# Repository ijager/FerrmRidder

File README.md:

# FerrmRidder

## Requirements

* Raspberry Pi 3 with Raspbian
* VL53L0X distance sensor
* Neopixel LED strip (WS2813)
* USB Audio output device (e.g. usb -> 3.5inch audio converter)
* Raspberry Pi breakout board with connectors for sensors (See Breakout directory)

## Installation Instructions

Download New Raspbian headless image and flash sd card

On a Mac:

```
diskutil unmountdisk /dev/disk2
sudo dd bs=2m if=2019-07-10-raspbian-buster-lite.img of=/dev/rdisk2
```

Boot raspberry pi and configure wifi and enable ssh and I2C

```
sudo raspi-config
```

Updates

```
sudo apt update && sudo apt upgrade
```

Install pip for python3
```
sudo apt-get install python3-pip
```

Install python dependencies, neopixel modules etc

```
sudo pip3 install rpi_ws281x adafruit-circuitpython-neopixel pygame libsdl-mixer1.2
sudo pip3 install adafruit-circuitpython-vl53l0x
sudo pip3 install adafruit-circuitpython-vl6180x
```

Then we'll follow [this Stackexchange](https://raspberrypi.stackexchange.com/questions/80072/how-can-i-use-an-external-usb-sound-card-and-set-it-as-default) answer to enable USB audio.

## send audio to pi

```
tar -czvf audio.tar.gz audio
scp audio.tar.gz pi@ip:~
```

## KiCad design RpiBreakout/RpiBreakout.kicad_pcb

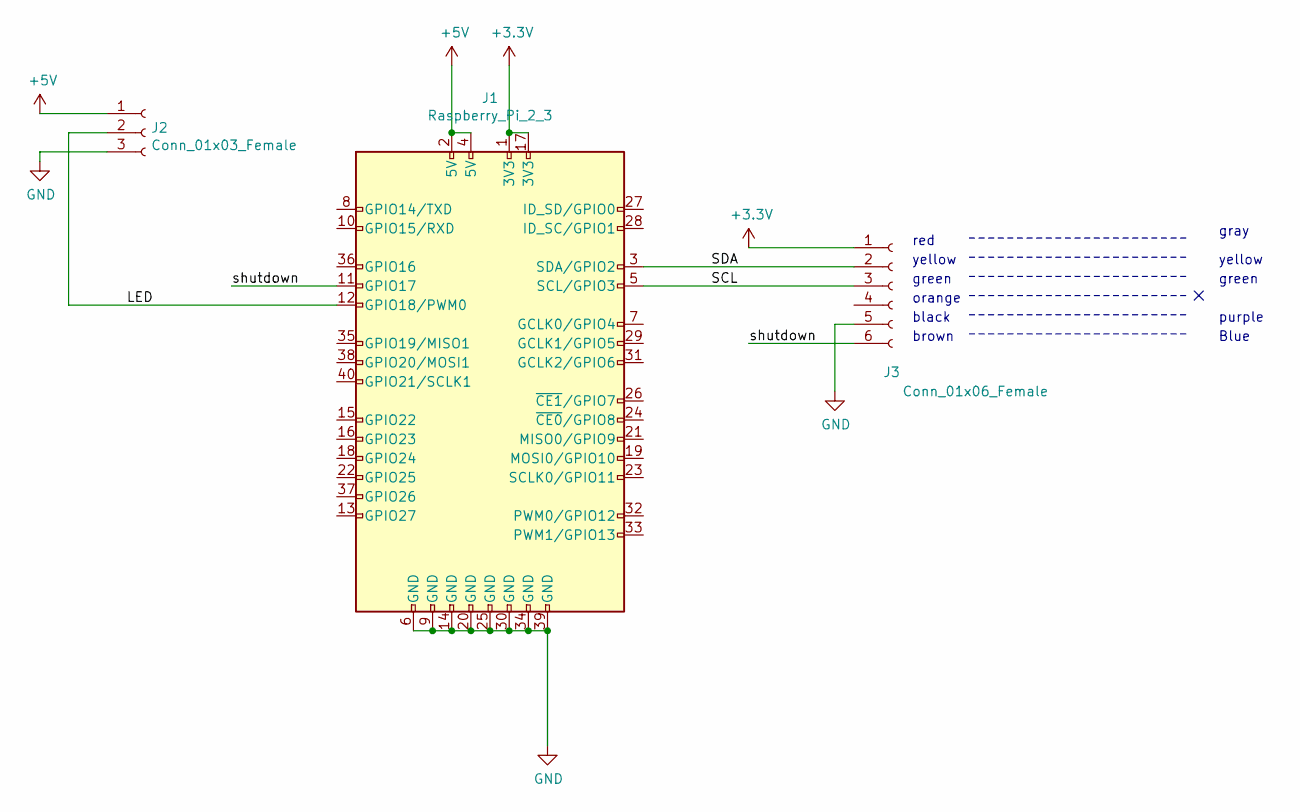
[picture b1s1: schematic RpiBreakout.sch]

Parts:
J1: Raspberry_Pi_2_3; PinSocket_2x20_P2.54mm_Vertical
J2: Conn_01x03_Female; PinSocket_1x03_P2.54mm_Vertical
J3: Conn_01x06_Female; PinSocket_1x06_P2.54mm_Vertical

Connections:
+3V3: J1.1 (3V3), J1.17 (3V3), J3.1
+5V: J1.2 (5V), J1.4 (5V), J2.1
/LED: J1.12 (GPIO18/PWM0), J2.2
/SCL: J1.5 (SCL/GPIO3), J3.3
/SDA: J1.3 (SDA/GPIO2), J3.2
/shutdown: J1.11 (GPIO17), J3.6
GND: J1.6 (GND), J1.9 (GND), J1.14 (GND), J1.20 (GND), J1.25 (GND), J1.30 (GND), J1.34 (GND), J1.39 (GND), J2.3, J3.5

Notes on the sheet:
red
yellow
green
black
orange
brown
gray
purple
Blue

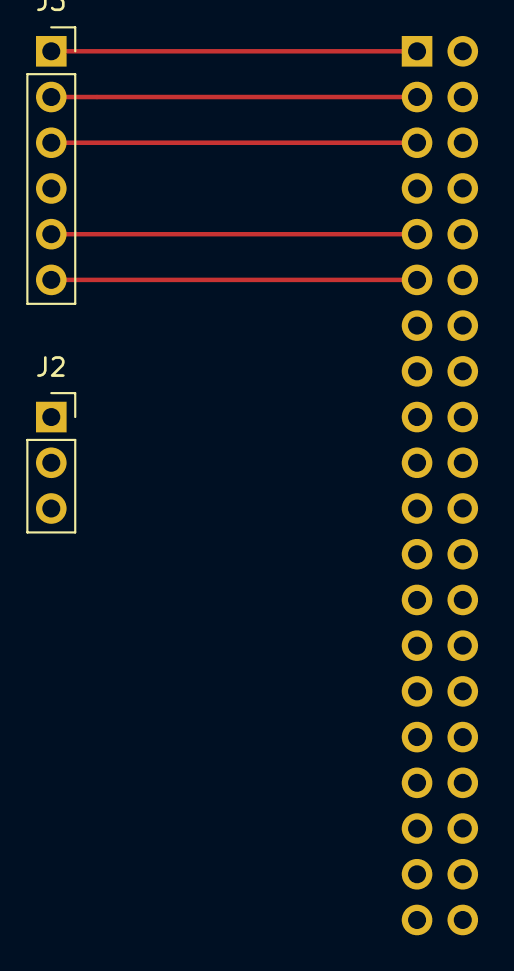
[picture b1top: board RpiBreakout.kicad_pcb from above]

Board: 4 copper layers, 3 parts (1 on the bottom side), 7 nets.

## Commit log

2019-08-20 Initial commit. Add breakout schematics
2019-08-20 Add examples for distance sensors
2019-08-20 Add pygame audio example
2019-08-20 Add leds example script
2019-08-20 Start audio library using pygame
2019-08-20 rename to src
2019-08-20 Extend test
2019-08-20 Add sensor and leds module
2019-08-21 Some bug fixes
2019-08-21 Make a simple demo application
2019-08-21 Small fix
2019-08-24 Add audio animations based on wav files
2019-08-24 Add some randomness to what type of animation is used
    1 out of 6 times (on average) we use randomColor crazy animation
2019-08-24 Stop previous sound if a new one is played
2019-08-24 Add Config on top of file and replace magic values
2019-08-24 Move config to separate file
2019-08-25 Rewrite to state machine
2019-08-25 Add idle animation (sine LED fade)
2019-08-25 Add bonus state
2022-08-17 Add Bonus state and startup sound
2022-08-17 Add systemd service and install script
2022-08-25 Fix install script
2022-08-25 Add try catch around sensor.get to prevent i2c crashes
2022-09-01 Change audio structure: add thankyou, intermezzo, startup dirs
    Also add fallback sound in case other sound fails
2022-09-01 Add sad.wav/pkl as fallback sound
2022-09-01 Add script for testing audio files
2022-09-01 Add improvements to randomly chosing wavfiles
    Too random is not good, so we'll keep a list of the last N choices.
2022-09-01 Add script to generate animation waveforms from wav files
2022-09-02 Change dankjewel to thankyou
